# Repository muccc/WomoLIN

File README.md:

use: git clone https://github.com/muccc/WomoLIN.git

# WomoLIN Hardware und sonstige Infos zum Projekt

Neue Wege in der konfigurierbaren Software Entwicklung eines Community Projektes

Alle Infos findet Ihr in unserem Wiki hier auf Github. 

https://github.com/muccc/WomoLIN/wiki/Home

# WomoLIN Meilensteine und Projektfortschritt

**18.Okt 2020  :** 100. Mitglied in unserer Telegramgruppe <br/>
**10.Aug 2020  :** Inbetriebnahme Controlboard 2.0.<br/>
**10.Juli 2020  :** Controlboard 2.0.<br/>
**10.Juni 2020  :** Beginn Einbau Controlboard in Womo von Jan.<br/>
**15.Mai 2020  :** Erstes Displayboard Kleinserie.<br/>
**11.Apr 2020  :** Erste Inbetriebnahme Display Unit mit Display.<br/>
**19.Mrz 2020  :** Die ersten Hardware für die Display Unit ist angekommen.<br/>
**16.Dez. bis 30.Dez.2019 :** 36th Chaos Communication Congress in Leipzig, Jan stellt die Hardware vor.<br/>
**10.Dez 2019  :** Die ersten Leiterplatten der Main Unit / Controlboard sind angekommen.<br/>
**03.Dez 2019  :** Der Schaltplan der Main Unit ist fertig gestellt.<br/> 

## **10.Aug 2020  :** Inbetriebnahme Controlboard 2.0.<br/>

## **10.Juli 2020  :** Controlboard 2.0.<br/>

## **10.Juni 2020  :** Beginn Einbau Controlboard in Womo von Jan.<br/>

## **15.Mai 2020  :** Erstes Displayboard Kleinserie.<br/>

## **11.Apr 2020  :** Erste Inbetriebnahme Display Unit mit Display.<br/>

## **19.Mrz 2020  :** Die ersten Hardware für die Display Unit ist angekommen.<br/>

## **16.Dez. bis 30.Dez.2019 :** 36th Chaos Communication Congress in Leipzig, Jan stellt die Hardware vor.<br/> 

## **10.Dez 2019  :** Die ersten Leiterplatten der Main Unit / Controlboard sind angekommen.<br/>

## **03.Dez 2019  :** Der Schaltplan der Main Unit ist fertig gestellt.<br/>

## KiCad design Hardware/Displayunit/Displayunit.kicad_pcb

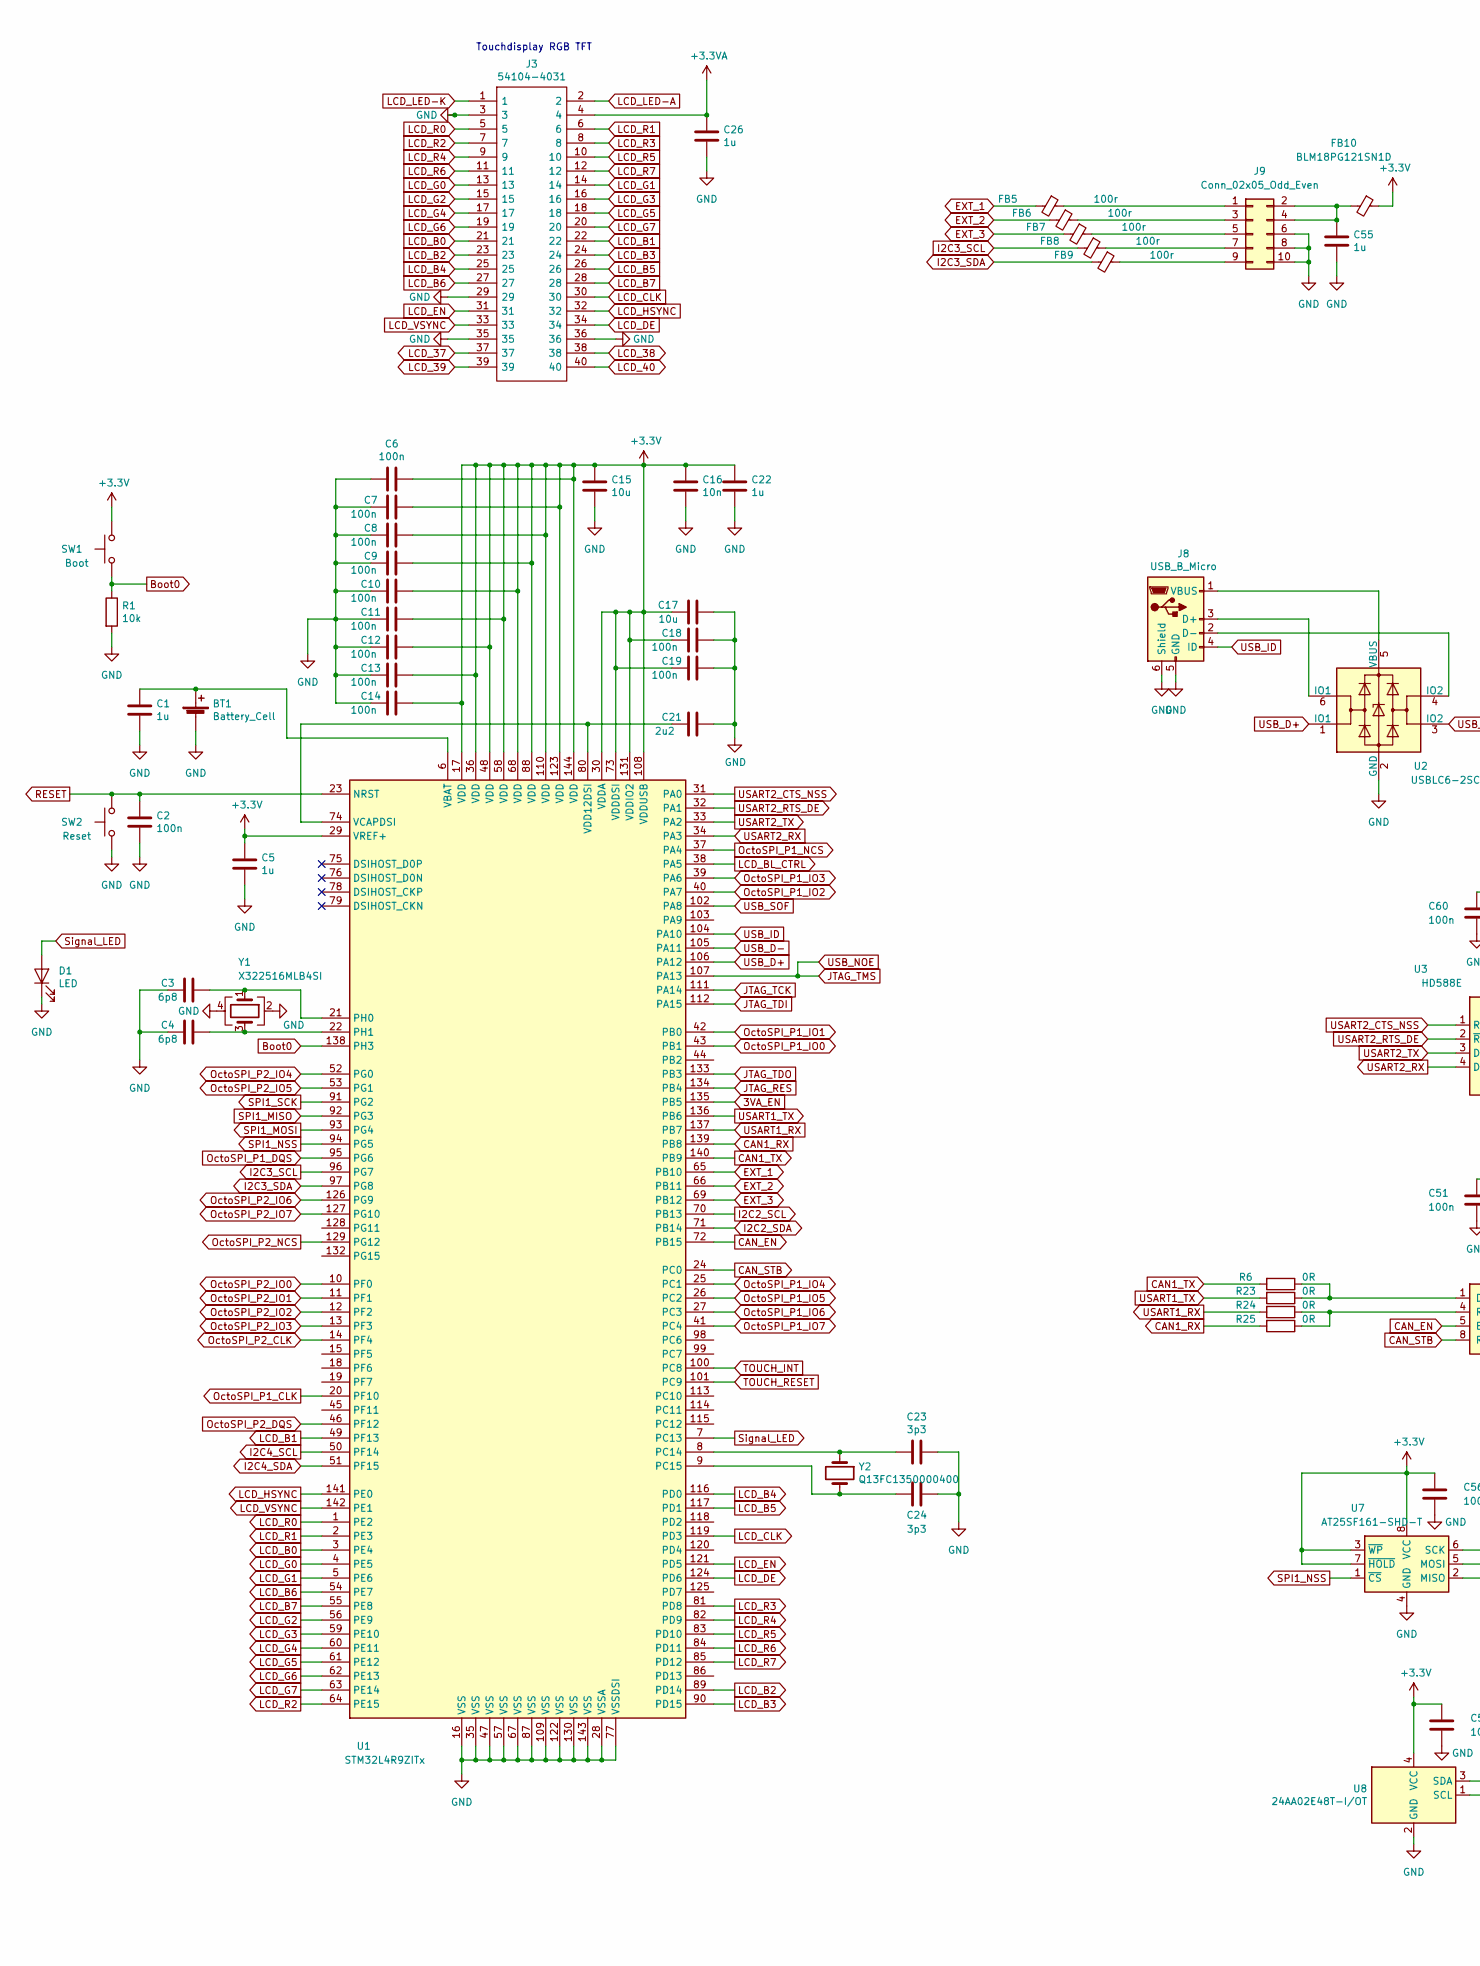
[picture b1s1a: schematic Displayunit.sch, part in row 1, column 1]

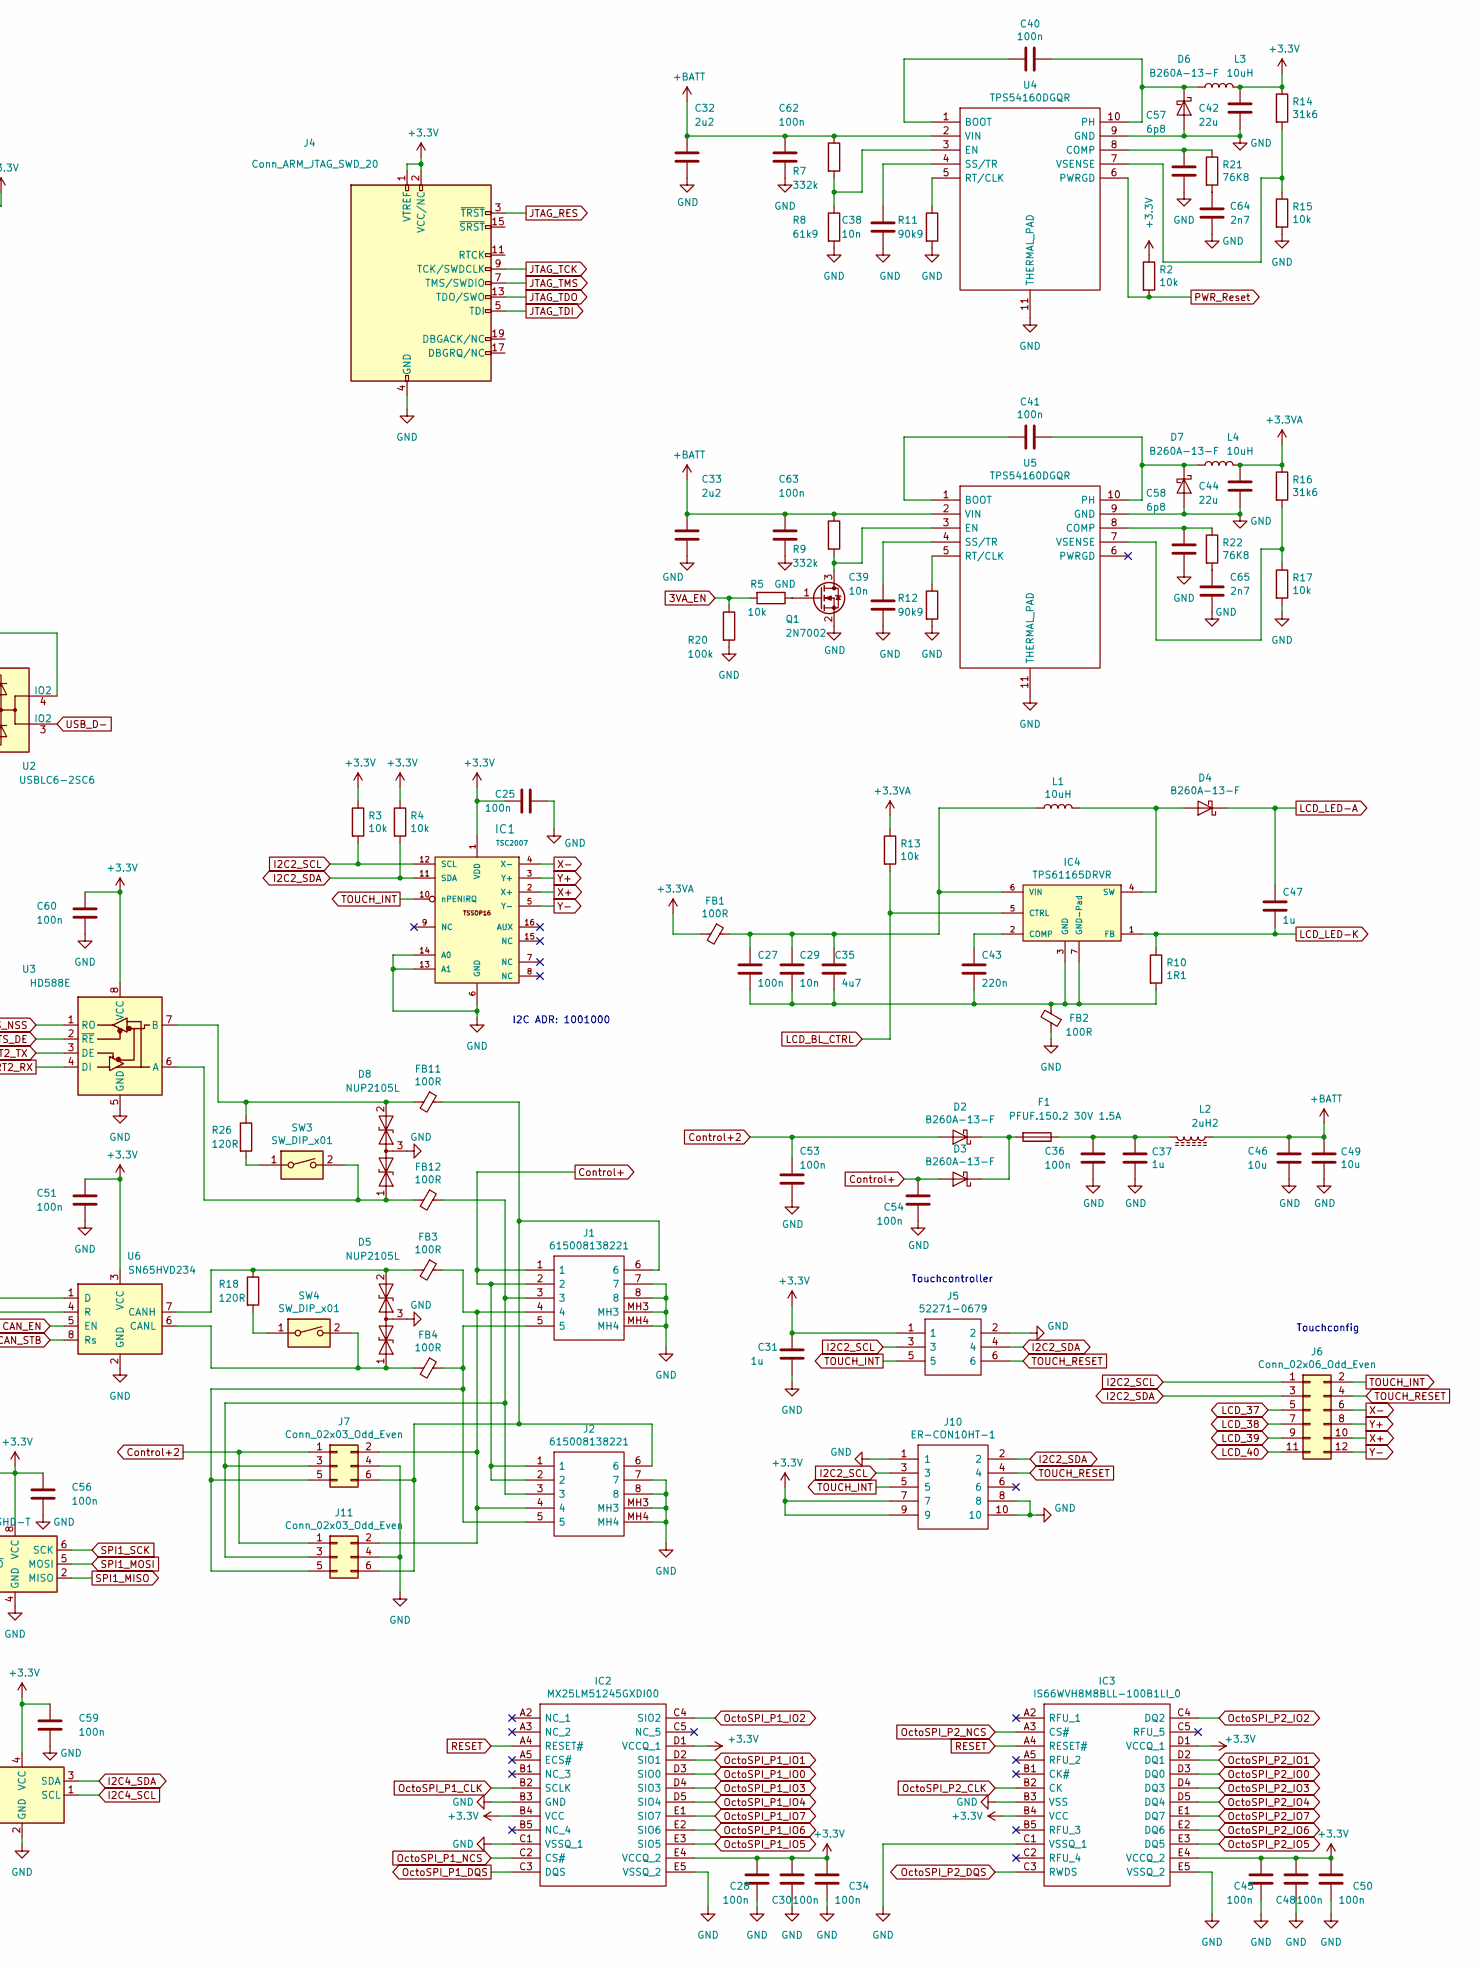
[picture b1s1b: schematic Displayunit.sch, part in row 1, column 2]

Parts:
BT1: Battery_Cell; QJ.BS-6
C1, C22, C26, C31, C37, C55: 1u; C_1206_3216Metric
C2, C6, C7, C8, C9, C10, C11, C12, C13, C14, C18, C19, C25, C27, C28, C30, C34, C36, C40, C41, C45, C48, C50, C51, C53, C54, C56, C59, C60, C62, C63: 100n; C_0603_1608Metric
C3, C4, C57, C58: 6p8; C_0603_1608Metric
C5: 1u; C_0603_1608Metric
C15, C17: 10u; C_1206_3216Metric
C16, C29, C38, C39: 10n; C_0603_1608Metric
C21, C32, C33: 2u2; C_1210_3225Metric
C23, C24: 3p3; C_0603_1608Metric
C35: 4u7; C_1210_3225Metric
C42, C44: 22u; C_1210_3225Metric
C43: 220n; C_0603_1608Metric
C46, C49: 10u; C_1210_3225Metric
C47: 1u; C_1210_3225Metric
C64, C65: 2n7; C_0603_1608Metric
D1: LED; LED_1206_3216Metric
D2, D3, D4, D6, D7: B260A-13-F; D_SMB
D5, D8: NUP2105L; SOT-23
F1: PFUF.150.2 30V 1.5A; Fuse_1210_3225Metric
FB1, FB2, FB3, FB4, FB11, FB12: 100R; L_0603_1608Metric
FB5, FB6, FB7, FB8, FB9: 100r; L_0603_1608Metric
FB10: BLM18PG121SN1D; L_0603_1608Metric
IC1: TSC2007; TSSOP-16_4.4x5mm_P0.65mm
IC2: MX25LM51245GXDI00; BGA24C100P5X5_600X800X35; Manufacturer_Part_Number MX25LM51245GXDI00
IC3: IS66WVH8M8BLL-100B1LI_0; BGA24C100P5X5_600X800X35; Manufacturer_Part_Number IS66WVH8M8BLL-100B1LI
IC4: TPS61165DRVR; WSON-6-1EP_2x2mm_P0.65mm_EP1x1.6mm_ThermalVias
J1, J2: 615008138221; Mouser Part Number 710-615008138221
J3: 54104-4031; Mouser Part Number 538-54104-4031
J4: Conn_ARM_JTAG_SWD_20; IDC-Header_2x10_P2.54mm_Vertical
J5: 52271-0679; Mouser Part Number 538-52271-0679
J6: Conn_02x06_Odd_Even; PinHeader_2x06_P2.54mm_Vertical
J7, J11: Conn_02x03_Odd_Even; Molex_Micro-Fit_3.0_43045-0612_2x03_P3.00mm_Vertical
J8: USB_B_Micro; USB_Micro-B_Molex-105017-0001
J9: Conn_02x05_Odd_Even; IDC-Header_2x05_P2.54mm_Vertical
J10: ER-CON10HT-1
L1, L3, L4: 10uH; MWSA0503
L2: 2uH2; MWSA0603
Q1: 2N7002; SOT-23
R1, R2, R3, R4, R5, R13, R15, R17: 10k; R_0603_1608Metric
R6, R23, R24, R25: 0R; R_0603_1608Metric
R7, R9: 332k; R_0603_1608Metric
R8: 61k9; R_0603_1608Metric
R10: 1R1; R_1206_3216Metric
R11, R12: 90k9; R_0603_1608Metric
R14, R16: 31k6; R_0603_1608Metric
R18, R26: 120R; R_0603_1608Metric
R20: 100k; R_0603_1608Metric
R21, R22: 76K8; R_0603_1608Metric
SW1: Boot; TS-1187A
SW2: Reset; TS-1187A
SW3, SW4: SW_DIP_x01; SW_SPST_CK_RS282G05A3
U1: STM32L4R9ZITx; LQFP-144_20x20mm_P0.5mm
U2: USBLC6-2SC6; SOT-23-6
U3: HD588E; SOIC-8_3.9x4.9mm_P1.27mm
U4, U5: TPS54160DGQR; SOP50P490X110-11N; Mouser Part Number 595-TPS54160DGQR
U6: SN65HVD234; SOIC-8_3.9x4.9mm_P1.27mm
U7: AT25SF161-SHD-T; SO-8_5.3x6.2mm_P1.27mm
U8: 24AA02E48T-I/OT; SOT-23-5
Y1: X322516MLB4SI; Crystal_SMD_3225-4Pin_3.2x2.5mm
Y2: Q13FC1350000400; Crystal_SMD_MicroCrystal_CC7V-T1A-2Pin_3.2x1.5mm

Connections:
3VA_EN: R5.2, R20.1, U1.135 (PB5)
+3.3VA: C26.1, C44.1, FB1.2, J3.4, L4.2, R13.1, R16.1
+3V3: C5.1, C6.1, C7.1, C8.1, C9.1, C10.1, C11.1, C12.1, C13.1, C14.1, C15.1, C16.1, C17.1, C18.2, C19.2, C22.1, C25.2, C28.1, C30.1, C31.1, C34.1, C42.1, C45.1, C48.1, C50.1, C51.1, C56.1, C59.1, C60.1, FB10.1, IC1.1 (VDD), IC2.B4 (VCC), IC2.D1 (VCCQ_1), IC2.E4 (VCCQ_2), IC3.B4 (VCC), IC3.D1 (VCCQ_1), IC3.E4 (VCCQ_2), J4.1 (VTREF), J4.2 (VCC/NC), J5.1, J10.7, J10.9, L3.2, R2.1, R3.1, R4.1, R14.1, SW1.2, U1.17 (VDD), U1.29 (VREF+), U1.30 (VDDA), U1.36 (VDD), U1.48 (VDD), U1.58 (VDD), U1.68 (VDD), U1.73 (VDDDSI), U1.88 (VDD), U1.108 (VDDUSB), U1.110 (VDD), U1.123 (VDD), U1.131 (VDDIO2), U1.144 (VDD), U3.8 (VCC), U6.3 (VCC), U7.3 (~WP), U7.7 (~HOLD), U7.8 (VCC), U8.4 (VCC)
+BATT: C32.1, C33.1, C46.1, C49.1, C62.1, C63.1, L2.1, R7.1, R9.1, U4.2 (VIN), U5.2 (VIN)
Boot0: R1.1, SW1.1, U1.138 (PH3)
CAN1_RX: R25.2, U1.139 (PB8)
CAN1_TX: R6.2, U1.140 (PB9)
CAN_EN: U1.72 (PB15), U6.5 (EN)
CAN_STB: U1.24 (PC0), U6.8 (Rs)
Control+: C54.1, D3.2 (A), J1.1, J1.2, J2.1, J2.2
Control+2: C53.1, D2.2 (A), J7.1, J11.1
EXT_1: FB5.2, U1.65 (PB10)
EXT_2: FB6.2, U1.66 (PB11)
EXT_3: FB7.2, U1.69 (PB12)
GND: BT1.2 (-), C1.2, C2.2, C3.2, C4.2, C5.2, C6.2, C7.2, C8.2, C9.2, C10.2, C11.2, C12.2, C13.2, C14.2, C15.2, C16.2, C17.2, C18.1, C19.1, C21.1, C22.2, C23.1, C24.1, C25.1, C26.2, C28.2, C30.2, C31.2, C32.2, C33.2, C34.2, C36.2, C37.2, C38.2, C39.2, C42.2, C44.2, C45.2, C46.2, C48.2, C49.2, C50.2, C51.2, C53.2, C54.2, C55.2, C56.2, C57.1, C58.1, C59.2, C60.2, C62.2, C63.2, C64.1, C65.1, D1.1 (K), D5.3 (common), D6.2 (A), D7.2 (A), D8.3 (common), FB2.1, IC1.6 (GND), IC1.13 (A1), IC1.14 (A0), IC2.B3 (GND), IC2.C1 (VSSQ_1), IC2.E5 (VSSQ_2), IC3.B3 (VSS), IC3.C1 (VSSQ_1), IC3.E5 (VSSQ_2), J1.7, J1.8, J1.MH3, J1.MH4, J2.7, J2.8, J2.MH3, J2.MH4, J3.3, J3.29, J3.35, J3.36, J4.4 (GND), J4.6 (GND), J4.8 (GND), J4.10 (GND), J4.12 (GND), J4.14 (GND), J4.16 (GND), J4.18 (GND), J4.20 (GND), J5.2, J7.4, J8.5 (GND), J8.6 (Shield), J9.6, J9.8, J9.10, J10.1, J10.8, J10.10, J11.4, Q1.2 (S), R1.2, R8.2, R11.2, R12.2, R15.2, R17.2, R20.2, SW2.1, U1.16 (VSS), U1.28 (VSSA), U1.35 (VSS), U1.47 (VSS), U1.57 (VSS), U1.67 (VSS), U1.77 (VSSDSI), U1.87 (VSS), U1.109 (VSS), U1.122 (VSS), U1.130 (VSS), U1.143 (VSS), U2.2 (GND), U3.5 (GND), U4.9 (GND), U4.11 (THERMAL_PAD), U5.9 (GND), U5.11 (THERMAL_PAD), U6.2 (GND), U7.4 (GND), U8.2 (GND), Y1.2, Y1.4
I2C2_SCL: IC1.12 (SCL), J5.3, J6.1, J10.3, R3.2, U1.70 (PB13)
I2C2_SDA: IC1.11 (SDA), J5.4, J6.3, J10.2, R4.2, U1.71 (PB14)
I2C3_SCL: FB8.2, U1.96 (PG7)
I2C3_SDA: FB9.2, U1.97 (PG8)
I2C4_SCL: U1.50 (PF14), U8.1 (SCL)
I2C4_SDA: U1.51 (PF15), U8.3 (SDA)
JTAG_RES: J4.3 (~TRST~), U1.134 (PB4)
JTAG_TCK: J4.9 (TCK/SWDCLK), U1.111 (PA14)
JTAG_TDI: J4.5 (TDI), U1.112 (PA15)
JTAG_TDO: J4.13 (TDO/SWO), U1.133 (PB3)
JTAG_TMS: J4.7 (TMS/SWDIO), U1.107 (PA13)
LCD_37: J3.37, J6.5
LCD_38: J3.38, J6.7
LCD_39: J3.39, J6.9
LCD_40: J3.40, J6.11
LCD_B0: J3.21, U1.3 (PE4)
LCD_B1: J3.22, U1.49 (PF13)
LCD_B2: J3.23, U1.89 (PD14)
LCD_B3: J3.24, U1.90 (PD15)
LCD_B4: J3.25, U1.116 (PD0)
LCD_B5: J3.26, U1.117 (PD1)
LCD_B6: J3.27, U1.54 (PE7)
LCD_B7: J3.28, U1.55 (PE8)
LCD_BL_CTRL: IC4.5 (CTRL), R13.2, U1.38 (PA5)
LCD_CLK: J3.30, U1.119 (PD3)
LCD_DE: J3.34, U1.124 (PD6)
LCD_EN: J3.31, U1.121 (PD5)
LCD_G0: J3.13, U1.4 (PE5)
LCD_G1: J3.14, U1.5 (PE6)
LCD_G2: J3.15, U1.56 (PE9)
LCD_G3: J3.16, U1.59 (PE10)
LCD_G4: J3.17, U1.60 (PE11)
LCD_G5: J3.18, U1.61 (PE12)
LCD_G6: J3.19, U1.62 (PE13)
LCD_G7: J3.20, U1.63 (PE14)
LCD_HSYNC: J3.32, U1.141 (PE0)
LCD_LED-A: C47.1, D4.1 (K), J3.2
LCD_LED-K: C47.2, IC4.1 (FB), J3.1, R10.1
LCD_R0: J3.5, U1.1 (PE2)
LCD_R1: J3.6, U1.2 (PE3)
LCD_R2: J3.7, U1.64 (PE15)
LCD_R3: J3.8, U1.81 (PD8)
LCD_R4: J3.9, U1.82 (PD9)
LCD_R5: J3.10, U1.83 (PD10)
LCD_R6: J3.11, U1.84 (PD11)
LCD_R7: J3.12, U1.85 (PD12)
LCD_VSYNC: J3.33, U1.142 (PE1)
unnamed: BT1.1 (+), C1.1, U1.6 (VBAT)
unnamed: C3.1, U1.21 (PH0), Y1.1
unnamed: C4.1, U1.22 (PH1), Y1.3
unnamed: C21.2, U1.74 (VCAPDSI), U1.80 (VDD12DSI)
unnamed: C23.2, U1.8 (PC14), Y2.1
unnamed: C24.2, U1.9 (PC15), Y2.2
unnamed: C27.1, C29.1, C35.1, FB1.1, IC4.6 (VIN), L1.1
unnamed: C27.2, C29.2, C35.2, C43.2, FB2.2, IC4.3 (GND), IC4.7 (GND-Pad), R10.2
unnamed: C36.1, C37.1, F1.1, L2.2
unnamed: C38.1, U4.4 (SS/TR)
unnamed: C39.1, U5.4 (SS/TR)
unnamed: C40.1, D6.1 (K), L3.1, U4.10 (PH)
unnamed: C40.2, U4.1 (BOOT)
unnamed: C41.1, D7.1 (K), L4.1, U5.10 (PH)
unnamed: C41.2, U5.1 (BOOT)
unnamed: C43.1, IC4.2 (COMP)
unnamed: C55.1, FB10.2, J9.2, J9.4
unnamed: C57.2, R21.1, U4.8 (COMP)
unnamed: C58.2, R22.1, U5.8 (COMP)
unnamed: C64.2, R21.2
unnamed: C65.2, R22.2
unnamed: D2.1 (K), D3.1 (K), F1.2
unnamed: D4.2 (A), IC4.4 (SW), L1.2
unnamed: D5.1 (A1), FB4.2, SW4.2, U6.6 (CANL)
unnamed: D5.2 (A2), FB3.2, R18.1, U6.7 (CANH)
unnamed: D8.1 (A1), FB12.2, SW3.2, U3.6 (A)
unnamed: D8.2 (A2), FB11.2, R26.1, U3.7 (B)
unnamed: FB3.1, J1.4, J2.4, J7.2, J11.2
unnamed: FB4.1, J1.5, J2.5, J7.5, J11.5
unnamed: FB5.1, J9.1
unnamed: FB6.1, J9.3
unnamed: FB7.1, J9.5
unnamed: FB8.1, J9.7
unnamed: FB9.1, J9.9
unnamed: FB11.1, J1.6, J2.6, J7.6, J11.6
unnamed: FB12.1, J1.3, J2.3, J7.3, J11.3
unnamed: J8.1 (VBUS), U2.5 (VBUS)
unnamed: J8.2 (D-), U2.4 (IO2)
unnamed: J8.3 (D+), U2.6 (IO1)
unnamed: Q1.1 (G), R5.1
unnamed: Q1.3 (D), R9.2, U5.3 (EN)
unnamed: R7.2, R8.1, U4.3 (EN)
unnamed: R11.1, U4.5 (RT/CLK)
unnamed: R12.1, U5.5 (RT/CLK)
unnamed: R14.2, R15.1, U4.7 (VSENSE)
unnamed: R16.2, R17.1, U5.7 (VSENSE)
unnamed: R18.2, SW4.1
unnamed: R6.1, R23.1, U6.1 (D)
unnamed: R24.1, R25.1, U6.4 (R)
unnamed: R26.2, SW3.1
OctoSPI_P1_CLK: IC2.B2 (SCLK), U1.20 (PF10)
OctoSPI_P1_DQS: IC2.C3 (DQS), U1.95 (PG6)
OctoSPI_P1_IO0: IC2.D3 (SIO0), U1.43 (PB1)
OctoSPI_P1_IO1: IC2.D2 (SIO1), U1.42 (PB0)
OctoSPI_P1_IO2: IC2.C4 (SIO2), U1.40 (PA7)
OctoSPI_P1_IO3: IC2.D4 (SIO3), U1.39 (PA6)
OctoSPI_P1_IO4: IC2.D5 (SIO4), U1.25 (PC1)
OctoSPI_P1_IO5: IC2.E3 (SIO5), U1.26 (PC2)
OctoSPI_P1_IO6: IC2.E2 (SIO6), U1.27 (PC3)
OctoSPI_P1_IO7: IC2.E1 (SIO7), U1.41 (PC4)
OctoSPI_P1_NCS: IC2.C2 (CS#), U1.37 (PA4)
OctoSPI_P2_CLK: IC3.B2 (CK), U1.14 (PF4)
OctoSPI_P2_DQS: IC3.C3 (RWDS), U1.46 (PF12)
OctoSPI_P2_IO0: IC3.D3 (DQ0), U1.10 (PF0)
OctoSPI_P2_IO1: IC3.D2 (DQ1), U1.11 (PF1)
OctoSPI_P2_IO2: IC3.C4 (DQ2), U1.12 (PF2)
OctoSPI_P2_IO3: IC3.D4 (DQ3), U1.13 (PF3)
OctoSPI_P2_IO4: IC3.D5 (DQ4), U1.52 (PG0)
OctoSPI_P2_IO5: IC3.E3 (DQ5), U1.53 (PG1)
OctoSPI_P2_IO6: IC3.E2 (DQ6), U1.126 (PG9)
OctoSPI_P2_IO7: IC3.E1 (DQ7), U1.127 (PG10)
OctoSPI_P2_NCS: IC3.A3 (CS#), U1.129 (PG12)
PWR_Reset: R2.2, U4.6 (PWRGD)
RESET: C2.1, IC2.A4 (RESET#), IC3.A4 (RESET#), SW2.2, U1.23 (NRST)
SPI1_MISO: U1.92 (PG3), U7.2 (MISO)
SPI1_MOSI: U1.93 (PG4), U7.5 (MOSI)
SPI1_NSS: U1.94 (PG5), U7.1 (~CS)
SPI1_SCK: U1.91 (PG2), U7.6 (SCK)
Signal_LED: D1.2 (A), U1.7 (PC13)
TOUCH_INT: IC1.10 (nPENIRQ), J5.5, J6.2, J10.5, U1.100 (PC8)
TOUCH_RESET: J5.6, J6.4, J10.4, U1.101 (PC9)
USART1_RX: R24.2, U1.137 (PB7)
USART1_TX: R23.2, U1.136 (PB6)
USART2_CTS_NSS: U1.31 (PA0), U3.1 (RO)
USART2_RTS_DE: U1.32 (PA1), U3.2 (~RE)
USART2_RX: U1.34 (PA3), U3.4 (DI)
USART2_TX: U1.33 (PA2), U3.3 (DE)
USB_D+: U1.106 (PA12), U2.1 (IO1)
USB_D-: U1.105 (PA11), U2.3 (IO2)
USB_ID: J8.4 (ID), U1.104 (PA10)
USB_SOF: U1.102 (PA8)
X+: IC1.2 (X+), J6.10
X-: IC1.4 (X-), J6.6
Y+: IC1.3 (Y+), J6.8
Y-: IC1.5 (Y-), J6.12

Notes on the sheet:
Touchdisplay RGB TFT
Touchcontroller
Touchconfig
I2C ADR: 1001000

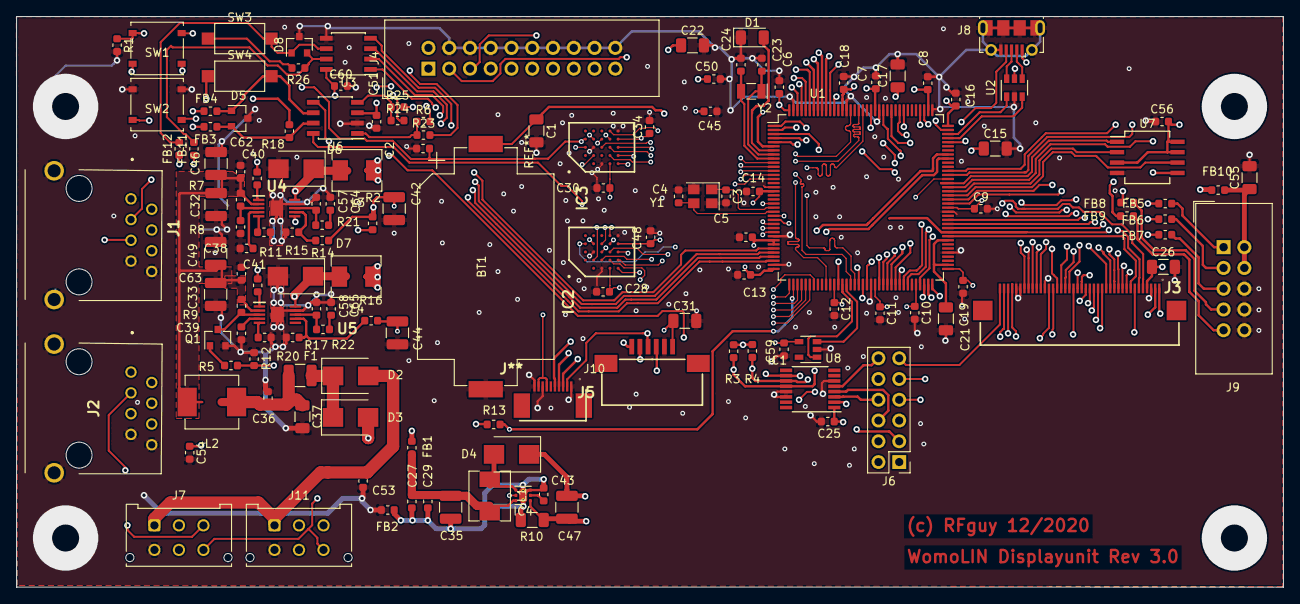
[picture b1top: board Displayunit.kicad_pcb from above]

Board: 4 copper layers, 155.0 x 69.8 mm, 143 parts (0 on the bottom side), 156 nets.

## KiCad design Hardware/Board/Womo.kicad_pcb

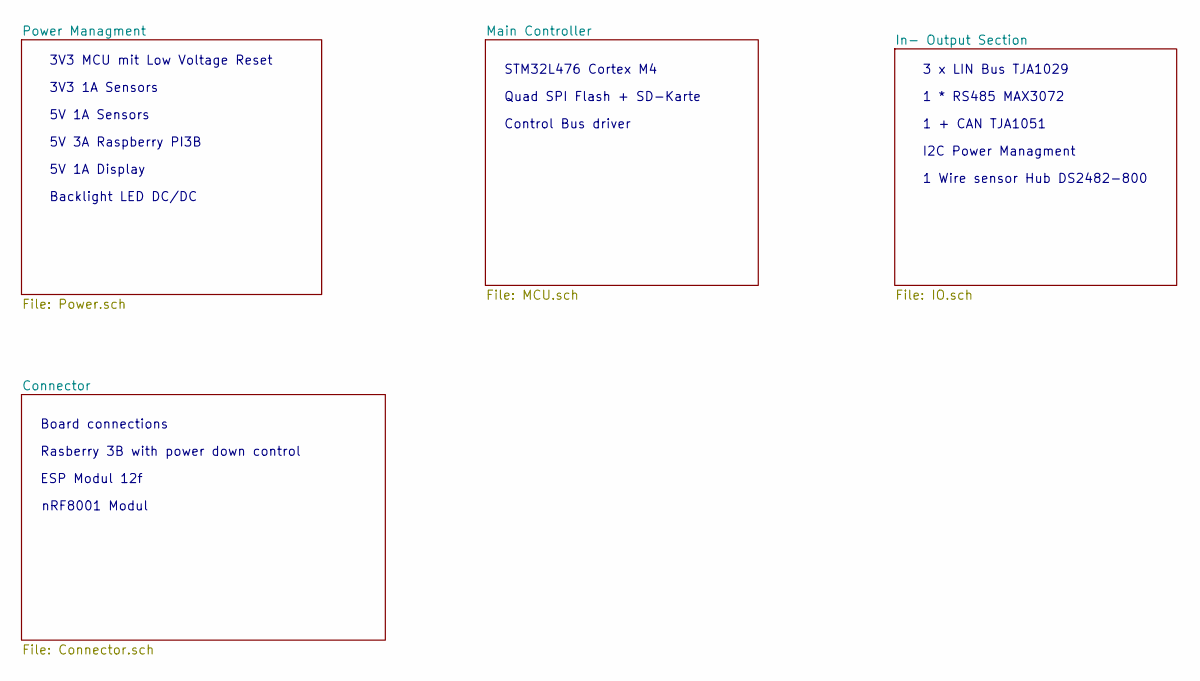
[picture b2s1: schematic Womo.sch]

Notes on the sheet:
3V3 MCU mit Low Voltage Reset
3V3 1A Sensors
5V 1A Sensors
5V 3A Raspberry PI3B
5V 1A Display
STM32L476 Cortex M4
Quad SPI Flash + SD-Karte
Control Bus driver
3 x LIN Bus TJA1029
1 * RS485 MAX3072
1 + CAN TJA1051
Rasberry 3B with power down control
ESP Modul 12f
1 Wire sensor Hub DS2482-800
Board connections
nRF8001 Modul
Backlight LED DC/DC
I2C Power Managment

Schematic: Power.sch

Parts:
C100, C105, C111, C120, C121: 2u2; C_1210_3225Metric
C101, C107, C112, C123, C124: 100nF; C_0603_1608Metric
C102, C113, C125, C126: 22uF; C_1210_3225Metric
C104, C110, C114: 5n6; C_0603_1608Metric
C106, C128: 100n; C_0603_1608Metric
C108: 10uF; C_1210_3225Metric
C109: 4u7; C_1210_3225Metric
C122: 22nF; C_0603_1608Metric
C127: 10u; C_1210_3225Metric
C129: 1u; C_0603_1608Metric
C130, C131: 47u; C_1210_3225Metric
D101, D102: B345BE-13; D_SMB
F1: KFZ 5A; Fuseholder_Blade_ATO_Littelfuse_Pudenz_2_Pin
L100, L101, L102: 15uH; L_Coilcraft_XxL4040
L104: 10uH; XAL8080
L105: L_Core_Ferrite; L_Coilcraft_XxL4020
Q100, Q102, Q103: 2N7002; SOT-23
R100: 3M3; R_0603_1608Metric
R101: 432k; R_0603_1608Metric
R102, R106, R107, R112, R113, R120: 40k2; R_0603_1608Metric
R103, R114: 86k6; R_0603_1608Metric
R104, R115: 32k4; R_0603_1608Metric
R105, R111, R119: 10k; R_0603_1608Metric
R108, R122: 4r7; R_0603_1608Metric
R109: 178k; R_0603_1608Metric
R110: 39k; R_0603_1608Metric
R121: 49k9; R_0603_1608Metric
R123: 105k; R_0603_1608Metric
R124: 22k6; R_0603_1608Metric
U100, U101, U102: MAX17572; DFN-12-1EP_3x3mm_P0.5mm_EP2.05x2.86mm
U104: MAX17574; QFN-24-1EP_4x5mm_P0.5mm_EP2.65x3.65mm

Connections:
3VA_EN: R112.1, R113.2; also elsewhere on the board
5V_EN: R105.1, R106.2; also elsewhere on the board
5V_Raspi_EN: R119.2; also elsewhere on the board
+3.3VA: C113.1, L102.2; also elsewhere on the board
+3V3: C102.1, L100.2, R103.1; also elsewhere on the board
+5V: C108.1, L101.2, R109.1, R110.1; also elsewhere on the board
+5VD: C125.1, C126.1, L104.2, R122.1, R123.1; also elsewhere on the board
+5VL: L105.2; also elsewhere on the board
+BATT: C100.1, C105.1, C111.1, C120.1, C121.1, C128.1, C129.1, R100.1, R107.1, R114.1, R120.1, U100.1, U101.1, U102.1, U104.5, U104.6, U104.7, U104.9; also elsewhere on the board
GND: C100.2, C102.2, C104.2, C105.2, C106.2, C108.2, C109.1, C110.2, C111.2, C113.2, C114.2, C120.2, C121.2, C122.2, C124.2, C125.2, C126.2, C127.1, C128.2, C129.2, C130.2, D101.1, D102.1, Q100.2, Q102.2, Q103.2, R101.2, R102.2, R104.2, R105.2, R108.2, R111.2, R112.2, R115.2, R121.2, R124.2, U100.5, U100.8, U100.9, U100.12, U100.13, U101.8, U101.12, U101.13, U102.5, U102.8, U102.9, U102.12, U102.13, U104.2, U104.3, U104.11, U104.21, U104.25; also elsewhere on the board
unnamed: C101.1, L100.1, U100.11
unnamed: C101.2, U100.10
unnamed: C104.1, U100.4
unnamed: C106.1, R109.2, U101.9
unnamed: C107.1, L101.1, U101.11
unnamed: C107.2, U101.10
unnamed: C109.2, U101.5
unnamed: C110.1, U101.4
unnamed: C112.1, L102.1, U102.11
unnamed: C112.2, U102.10
unnamed: C114.1, U102.4
unnamed: C122.1, U104.16
unnamed: C123.1, L104.1, U104.1, U104.23, U104.24
unnamed: C123.2, U104.22
unnamed: C124.1, R122.2, U104.20
unnamed: C127.2, U104.12
unnamed 125: C130.1; also elsewhere on the board
unnamed 126: C131.1, L105.1; also elsewhere on the board
unnamed 127: C131.2; also elsewhere on the board
unnamed 148: D101.2, D102.2; also elsewhere on the board
unnamed: Q100.1, R106.1
unnamed: Q100.3, R107.2, U101.2
unnamed: Q102.1, R113.1
unnamed: Q102.3, R114.2, U102.2
unnamed: Q103.1, R119.1
unnamed: Q103.3, R120.2, U104.10
unnamed: R100.2, R101.1, U100.2
unnamed: R102.1, U100.6
unnamed: R103.2, R104.1, U100.7
unnamed: R108.1, U101.6
unnamed: R110.2, R111.1, U101.7
unnamed: R115.1, U102.6
unnamed 346: U102.7; also elsewhere on the board
unnamed: R121.1, U104.19
unnamed: R123.2, R124.1, U104.18
PWR_Reset: U100.3; also elsewhere on the board

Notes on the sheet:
3V3 1A Main CPU Supply
5V 1A Peripheral Supply
3V3 1A Peripheral Supply
5V 3A Rasberry Pi Supply
5V 3A Modem / GNSS Supply
DC 10-30V Input Filter and Fuse

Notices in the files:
parts and their libraries:
Copyright 2016 Accelerated Designs. All rights reserved.
